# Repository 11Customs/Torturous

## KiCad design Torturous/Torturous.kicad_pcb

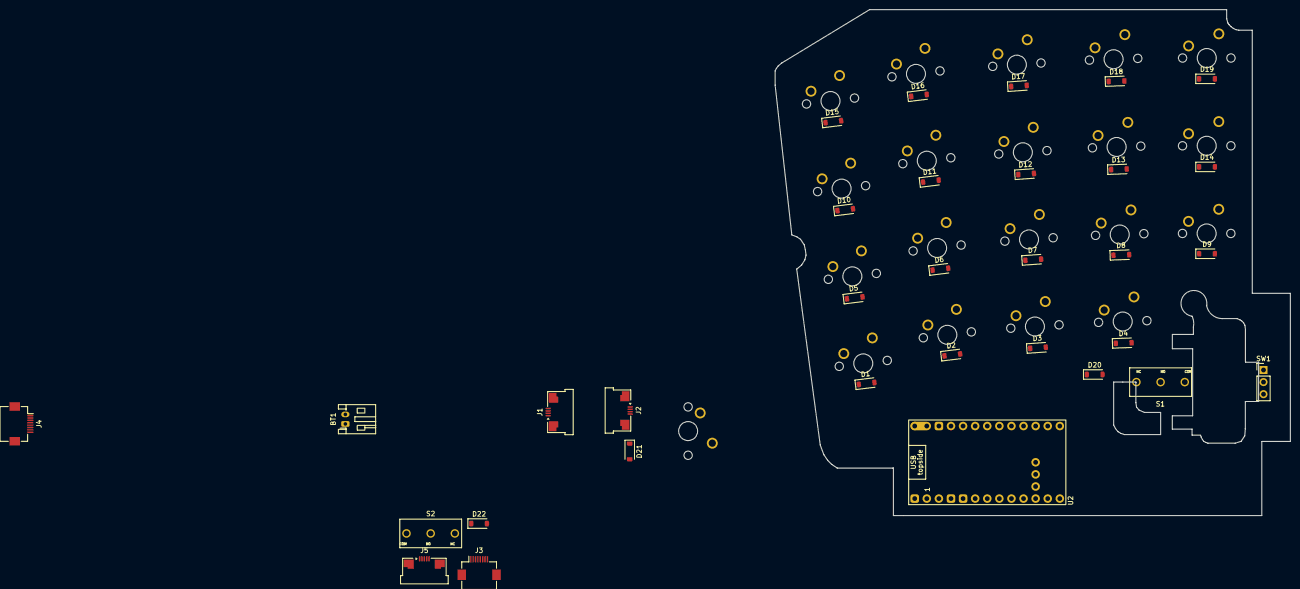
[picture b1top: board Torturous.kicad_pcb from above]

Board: 2 copper layers, 108.2 x 106.3 mm, 52 parts (0 on the bottom side), 47 nets, no tracks yet.

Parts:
BT1: Battery; JST_PH_S2B-PH-K_1x02_P2.00mm_Horizontal
D1, D2, D3, D4, D5, D6, D7, D8, D9, D10, D11, D12, D13, D14, D15, D16, D17, D18, D19, D20, D21, D22: 1N4148W; D_SOD-123
J1, J2: Conn_01x04_Pin; Amphenol_F32Q-1A7x1-11004_1x04-1MP_P0.5mm_Horizontal
J3, J4: Conn_01x08_Pin; Hirose_FH12-8S-0.5SH_1x08-1MP_P0.50mm_Horizontal
J5: Conn_01x05_Pin; Amphenol_F32Q-1A7x1-11005_1x05-1MP_P0.5mm_Horizontal
MX1, MX2, MX3, MX4, MX5, MX6, MX7, MX8, MX9, MX10, MX11, MX12, MX13, MX14, MX15, MX16, MX17, MX18, MX19, MX20: MX_SW_solder; SW_MX_1u
S1, S2: 463091370402
SW1: RotaryEncoder; PinHeader_1x03_P2.54mm_Vertical
U2: nice_nano; nice_nano_AH_USBup

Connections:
/COL1: MX1.1, MX6.1, MX11.1, MX16.1, U2.9 (P1.00)
/COL2: MX2.1, MX7.1, MX12.1, MX17.1, U2.10 (P0.11)
/COL3: MX3.1, MX8.1, MX13.1, MX18.1, U2.22 (P1.11-LF)
/COL4: MX4.1, MX9.1, MX14.1, MX19.1, U2.23 (P0.10-LF)
/COL5: MX5.1, MX10.1, MX15.1, S1.1, U2.24 (P0.09-LF)
/COL6: J1.2, J4.7, U2.21 (P1.13-LF)
/ROW1: D15.1 (K), D16.1 (K), D17.1 (K), D18.1 (K), D19.1 (K), U2.8 (P0.24)
/ROW2: D10.1 (K), D11.1 (K), D12.1 (K), D13.1 (K), D14.1 (K), U2.7 (P0.22)
/ROW3: D5.1 (K), D6.1 (K), D7.1 (K), D8.1 (K), D9.1 (K), J4.6, U2.6 (P0.20)
/ROW4: D1.1 (K), D2.1 (K), D3.1 (K), D4.1 (K), D20.1 (K), J1.1, U2.5 (P0.17)
unnamed: BT1.1 (+), U2.13 (BAT+)
unnamed: BT1.2 (-), U2.14 (GND)
unnamed: D1.2 (A), MX16.2
unnamed: D2.2 (A), MX17.2
unnamed: D3.2 (A), MX18.2
unnamed: D4.2 (A), MX19.2
unnamed: D5.2 (A), MX11.2
unnamed: D6.2 (A), MX12.2
unnamed: D7.2 (A), MX13.2
unnamed: D8.2 (A), MX14.2
unnamed: D9.2 (A), MX15.2
unnamed: D10.2 (A), MX6.2
unnamed: D11.2 (A), MX7.2
unnamed: D12.2 (A), MX8.2
unnamed: D13.2 (A), MX9.2
unnamed: D14.2 (A), MX10.2
unnamed: D15.2 (A), MX1.2
unnamed: D16.2 (A), MX2.2
unnamed: D17.2 (A), MX3.2
unnamed: D18.2 (A), MX4.2
unnamed: D19.2 (A), MX5.2
unnamed: D20.2 (A), S1.2
unnamed: D21.2 (A), MX20.2
unnamed: D21.1 (K), J2.1
unnamed: D22.2 (A), S2.2
unnamed: D22.1 (K), J3.6
unnamed: J2.2, MX20.1
unnamed: J3.1, J5.4
unnamed: J3.2, J5.2
unnamed: J3.3, J5.5
unnamed: J3.4, J5.1
unnamed: J3.5, J5.3
unnamed: J3.7, S2.1
unnamed: J4.1, U2.16 (3V3)
unnamed: J4.3, U2.17 (P0.31-LF)
unnamed: J4.4, U2.18 (P0.29-LF)
unnamed: J4.5, U2.20 (P1.15-LF)

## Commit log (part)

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2026-06-02 MCU, basic matrix and battery
2026-06-05 finnished v0.1 schematics
